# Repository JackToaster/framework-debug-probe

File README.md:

# framework Debug Probe

Debug probe built to run a fork of the [Black Magic Probe](https://github.com/JackToaster/blackmagic) firmware, and fit in an expansion bay of a Framework laptop.

Supports programming and debugging a wide range of ARM microcontroller targets over JTAG and SWD.

#
Framework Debug Probe © 2023 by Jack LeFevre is licensed under [CC BY-SA 4.0 ](http://creativecommons.org/licenses/by-sa/4.0/)

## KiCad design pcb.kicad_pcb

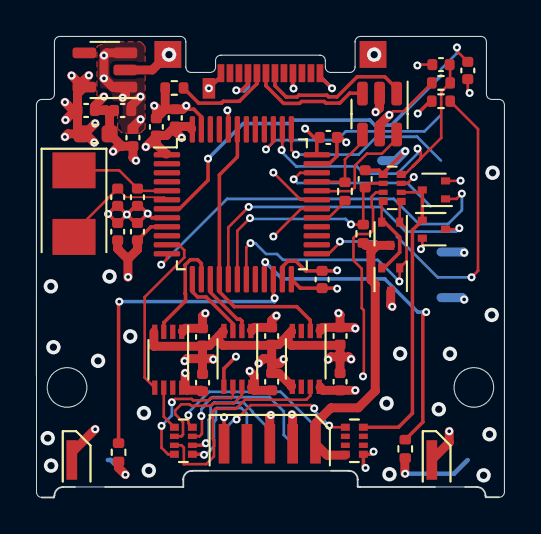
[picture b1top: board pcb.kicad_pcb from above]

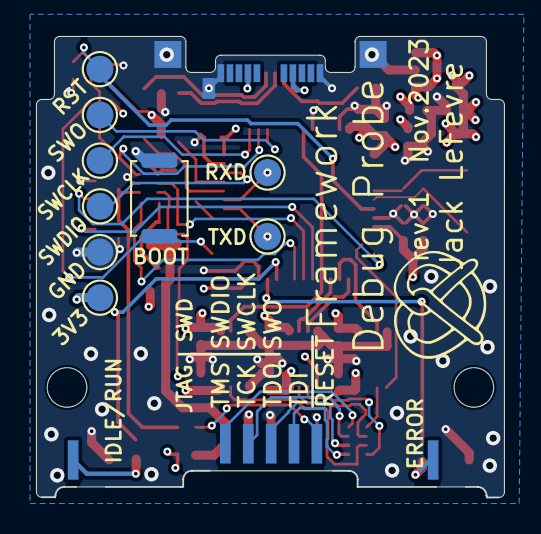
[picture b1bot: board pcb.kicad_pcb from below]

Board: 4 copper layers, 26.0 x 25.6 mm, 62 parts (11 on the bottom side), 46 nets.

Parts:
C1, C2: 30p; C_0402_1005Metric
C3: 4u7; C_0603_1608Metric
C4, C5, C6, C7, C8, C10, C11, C13, C17, C18, C19, C21, C22, C23, C24: 100n; C_0402_1005Metric
C9, C14, C15: 1u; C_0402_1005Metric
D2: Orange; LED_THT_Edge Mount
D3: Red; LED_THT_Edge Mount
H1, H2: MountingHole; MountingHole_2.2mm_M2
J2: Conn_ARM_JTAG_SWD_10; Cortex-10pin-sidemount
NT1: NetTie_2; NetTie-2_SMD_Pad0.5mm
P1: USB_C_Plug; USB_C_Plug_Molex_105444
Q1, Q2: CJE3139K; SOT-523
Q5, Q6: 2N7002; SOT-523
R1: 5.1k; R_0402_1005Metric
R4: 220k; R_0402_1005Metric
R5, R21: 4k7; R_0402_1005Metric
R7: 1k5; R_0402_1005Metric
R9, R10: 330R; R_0402_1005Metric
RN1, RN2: 121R; R_Array_Convex_4x0402
RN3: 10k; R_Array_Convex_4x0402
SW1: SW_Push; SW_Push_SPST_NO_Alps_SKRK
TP1, TP2, TP3, TP4: TestPoint; TestPoint_Pad_1.5x1.5mm
TP5, TP6, TP7, TP8, TP9, TP10, TP11, TP12: TestPoint; TestPoint_Pad_D1.5mm
U1: WE-TVS-82400102; SOT-23-6
U2: STM32F103C8T6; LQFP-48_7x7mm_P0.5mm
U6, U7, U8: 74LVC2T45DC; VSSOP-8_2.3x2mm_P0.5mm
U9: AP2112K-3.3; SOT-23-5
Y1: 8MHz; Crystal_SMD_5032-2Pin_5.0x3.2mm

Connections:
+3V3: C3.1, C4.1, C5.1, C6.1, C8.1, C15.1, C17.1, C18.1, C19.1, NT1.1, Q1.3, R4.2, TP10.1, U2.1 (VBAT), U2.24 (VDD), U2.36 (VDD), U2.48 (VDD), U6.1 (VCCA), U6.5 (DIR), U7.1 (VCCA), U8.1 (VCCA), U9.5 (VOUT)
/HSE_IN: C2.1, U2.6 (PD1), Y1.2
/HSE_OUT: C1.1, U2.5 (PD0), Y1.1
/RST: J2.10 (~RESET), RN2.1 (R1.1)
/SSD+: P1.A6 (D+), U1.3
/SSD-: P1.A7 (D-), U1.1
/TCK: J2.4 (SWDCLK/TCK), RN1.3 (R3.1)
/TDI: J2.8 (NC/TDI), RN1.1 (R1.1)
/TDO: J2.6 (SWO/TDO), RN1.2 (R2.1)
/TMS: J2.2 (SWDIO/TMS), RN1.4 (R4.1)
/USB_PU: R7.1, U2.29 (PA8)
GND: C1.2, C2.2, C3.2, C4.2, C5.2, C6.2, C7.2, C8.2, C9.2, C10.2, C11.2, C13.2, C14.2, C15.2, C17.2, C18.2, C19.2, C21.2, C22.2, C23.2, C24.2, D2.1 (K), D3.1 (K), J2.3 (GND), J2.5 (GND), J2.9 (GNDDetect), P1.A1 (GND), P1.A12 (GND), P1.B1 (GND), P1.B12 (GND), P1.S1 (SHIELD), Q5.2 (S), Q6.2 (S), R1.2, RN3.1 (R1.1), RN3.7 (R2.2), SW1.1, TP1.1, TP2.1, TP3.1, TP4.1, TP9.1, U1.2, U2.8 (VSSA), U2.23 (VSS), U2.35 (VSS), U2.44 (BOOT0), U2.47 (VSS), U6.4 (GND), U7.4 (GND), U7.5 (DIR), U8.4 (GND), U9.2 (GND)
LED1: R9.1, U2.21 (PB10)
LED2: R10.1, U2.22 (PB11)
unnamed: D2.2 (A), R9.2
unnamed: D3.2 (A), R10.2
unnamed: P1.A5 (CC), R1.1
unnamed: Q1.2, Q2.2, RN3.4 (R4.1)
unnamed: R4.1, SW1.2, U2.25 (PB12)
PWR_BR: Q1.1, Q2.1, RN3.5 (R4.2), U2.19 (PB1)
RST_SENSE: Q6.3 (D), U2.17 (PA7)
SWCLK: TP6.1, U2.37 (PA14)
SWDIO: TP7.1, U2.34 (PA13)
SWO: TP8.1, U2.39 (PB3)
TMS_DIR: U2.11 (PA1), U8.5 (DIR)
TPWR: J2.1 (VTref), Q2.3, R21.2, RN2.4 (R4.1)
TPWR_MEAS: C24.1, R21.1, RN3.2 (R2.1), U2.18 (PB0)
USB_D+: R7.2, U1.4, U2.33 (PA12)
USB_D-: U1.6, U2.32 (PA11)
VBUS: C11.1, C14.1, P1.A4 (VBUS), P1.A9 (VBUS), P1.B4 (VBUS), P1.B9 (VBUS), R5.2, U1.5, U9.1 (VIN), U9.3 (EN)
VBUS_MEAS: C13.1, R5.1, RN3.8 (R1.2), U2.38 (PA15)
VDDA: C9.1, C10.1, NT1.2, U2.9 (VDDA)
iRST: Q5.1 (G), U2.12 (PA2)
iRXD: TP12.1, U2.31 (PA10)
iTCK: U2.15 (PA5), U6.2 (1A)
iTDI: U2.13 (PA3), U6.3 (2A)
iTDO: U2.16 (PA6), U2.43 (PB7), U7.2 (1A)
iTMS: U2.14 (PA4), U8.3 (2A)
iTXD: TP11.1, U2.30 (PA9)
nRST: C7.1, TP5.1, U2.7 (NRST)
xRST: Q5.3 (D), Q6.1 (G), RN2.8 (R1.2), RN3.6 (R3.2)
xTCK: RN1.6 (R3.2), U6.7 (1B)
xTDI: RN1.8 (R1.2), U6.6 (2B)
xTDO: RN1.7 (R2.2), U7.7 (1B)
xTMS: RN1.5 (R4.2), U8.6 (2B)
xTPWR: C21.1, C22.1, C23.1, RN2.5 (R4.2), RN3.3 (R3.1), U6.8 (VCCB), U7.8 (VCCB), U8.8 (VCCB)

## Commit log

2023-11-04 Corrected USB resistors
2023-11-04 Added 3d models for enclosure
2023-11-04 dim leds
2023-11-04 update led footprint
